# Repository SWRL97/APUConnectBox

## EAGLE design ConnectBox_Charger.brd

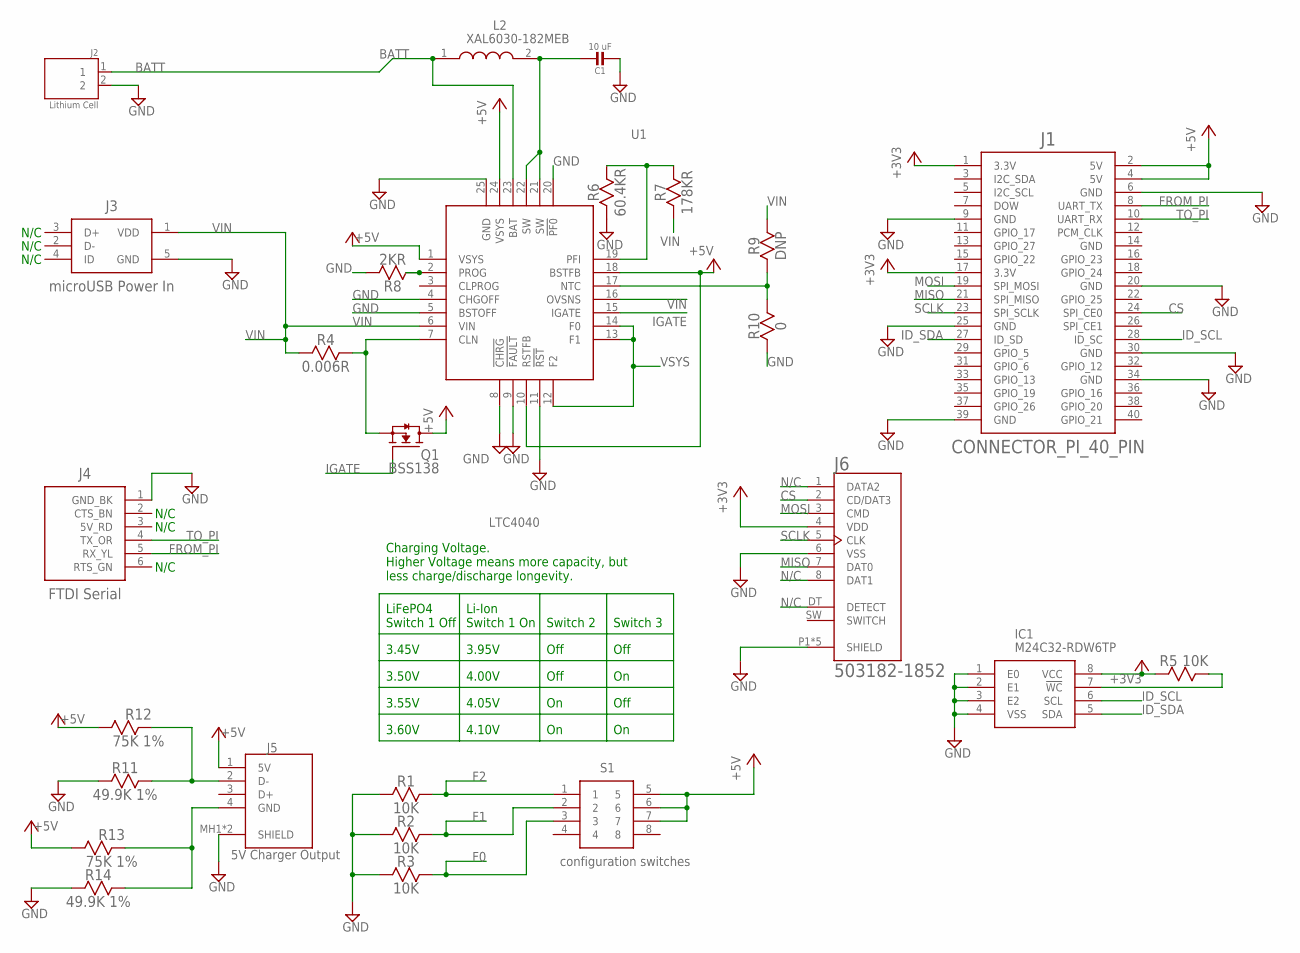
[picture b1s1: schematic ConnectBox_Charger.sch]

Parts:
C1: 10 uF; MICROBUILDER_0805_10MGAP
IC1: M24C32-RDW6TP; SOP65P640X120-8N
J1: CONNECTOR_PI_40_PIN; 2X20
J2: Lithium Cell; JST_S2B-PH-SM4-TB(LF)(SN)
J3: microUSB Power In; FRAMATOME_10118194-0001LF
J4: FTDI Serial; ESQ-106-XX-X-S
J5: 5V Charger Output; SS52100001
J6: 503182-1852; MOLEX_503182-1852
L2: XAL6030-182MEB; XAL6030182MEB
Q1: BSS138
R1, R2, R3, R5: 10K; RESC1608X55L25N
R4: 0.006R; RESC1608X55L25N
R6: 60.4KR; RESC1608X55L25N
R7: 178KR; RESC1608X55L25N
R8: 2KR; RESC1608X55L25N
R9: DNP; RESC1608X55L25N
R10: 0; RESC1608X55L25N
R11, R14: 49.9K 1%; RESC1608X55L25N
R12, R13: 75K 1%; RESC1608X55L25N
S1: configuration switches; 219-4LPST
U1: LTC4040; QFN50P500X400X80-25N

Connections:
+3V3: IC1.8 (VCC), J1.1 (3.3V), J1.17 (3.3V), J6.4 (VDD), R5.2
+5V: J1.2 (5V), J1.4 (5V), J5.1 (5V), Q1.D, R12.2, R13.2, S1.5, S1.6, S1.7, U1.1 (VSYS), U1.10 (RSTFB), U1.18 (BSTFB), U1.24 (VSYS)
BATT: J2.1, L2.1, U1.23 (BAT)
CS: J1.24 (SPI_CE0), J6.2 (CD/DAT3)
F0: R3.2, S1.3
F1: R2.2, S1.2
F2: R1.2, S1.1
FROM_PI: J1.8 (UART_TX), J4.5 (RX_YL)
GND: C1.2, IC1.1 (E0), IC1.2 (E1), IC1.3 (E2), IC1.4 (VSS), J1.6 (GND), J1.9 (GND), J1.20 (GND), J1.25 (GND), J1.30 (GND), J1.34 (GND), J1.39 (GND), J2.2, J3.5 (GND), J4.1 (GND_BK), J5.MH1 (SHIELD), J5.MH2 (SHIELD), J6.6 (VSS), J6.P1 (SHIELD), J6.P2 (SHIELD), J6.P3 (SHIELD), J6.P4 (SHIELD), J6.P5 (SHIELD), R1.1, R2.1, R3.1, R6.1, R8.2, R10.1, R11.2, R14.2, U1.4 (CHGOFF), U1.5 (BSTOFF), U1.8 (!CHRG), U1.9 (!FAULT), U1.11 (!RST), U1.20 (!PF0), U1.25 (GND)
ID_SCL: IC1.6 (SCL), J1.28 (ID_SC)
ID_SDA: IC1.5 (SDA), J1.27 (ID_SD)
IGATE: Q1.G, U1.15 (IGATE)
MISO: J1.21 (SPI_MISO), J6.7 (DAT0)
MOSI: J1.19 (SPI_MOSI), J6.3 (CMD)
unnamed: Q1.S, R4.2, U1.7 (CLN)
unnamed: IC1.7 (!WC), R5.1
unnamed: R6.2, R7.2, U1.19 (PFI)
unnamed: C1.1, L2.2, U1.21 (SW), U1.22 (SW)
unnamed: R8.1, U1.2 (PROG)
unnamed: J5.4 (GND), R13.1, R14.1
unnamed: R9.1, R10.2, U1.17 (NTC)
unnamed: J5.2 (D-), R11.1, R12.1
N/C: J6.1 (DATA2), J6.8 (DAT1), J6.DT (DETECT)
SCLK: J1.23 (SPI_SCLK), J6.5 (CLK)
TO_PI: J1.10 (UART_RX), J4.4 (TX_OR)
VIN: J3.1 (VDD), R4.1, R7.1, R9.2, U1.6 (VIN), U1.16 (OVSNS)
VSYS: U1.12 (F2), U1.13 (F1), U1.14 (F0)

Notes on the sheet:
N/C
Li-Ion Switch 1 On
Switch 3
LiFePO4 Switch 1 Off
Off
Switch 2
3.45V
3.95V
3.50V
4.00V
3.55V
4.05V
3.60V
4.10V
Charging Voltage. Higher Voltage means more capacity, but less charge/discharge longevity.

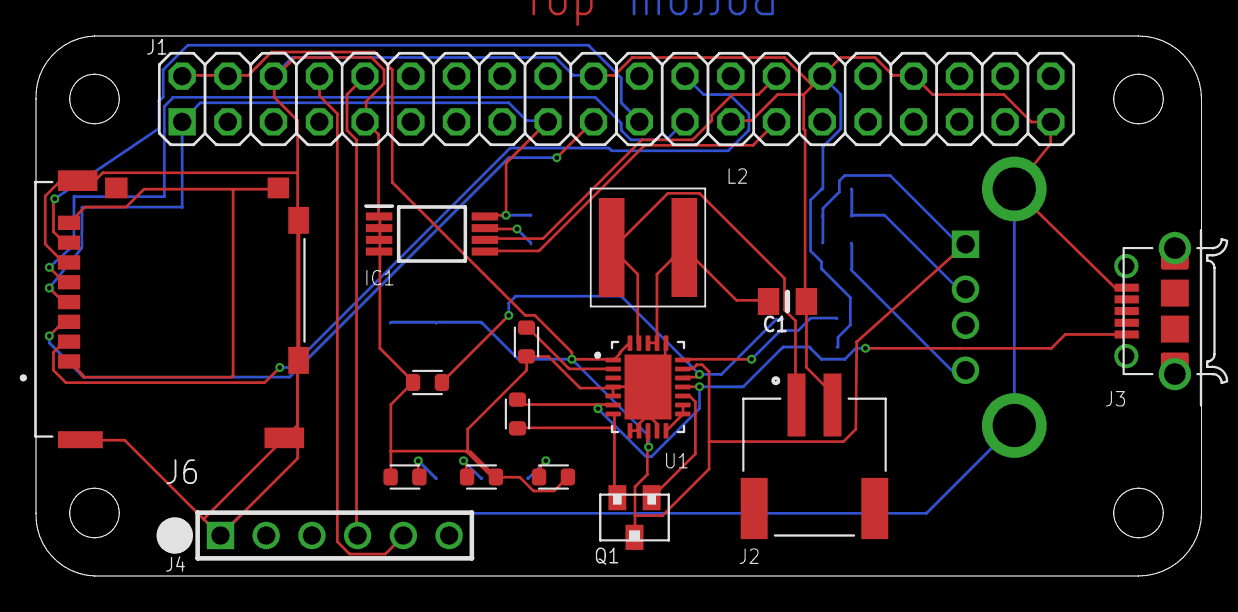
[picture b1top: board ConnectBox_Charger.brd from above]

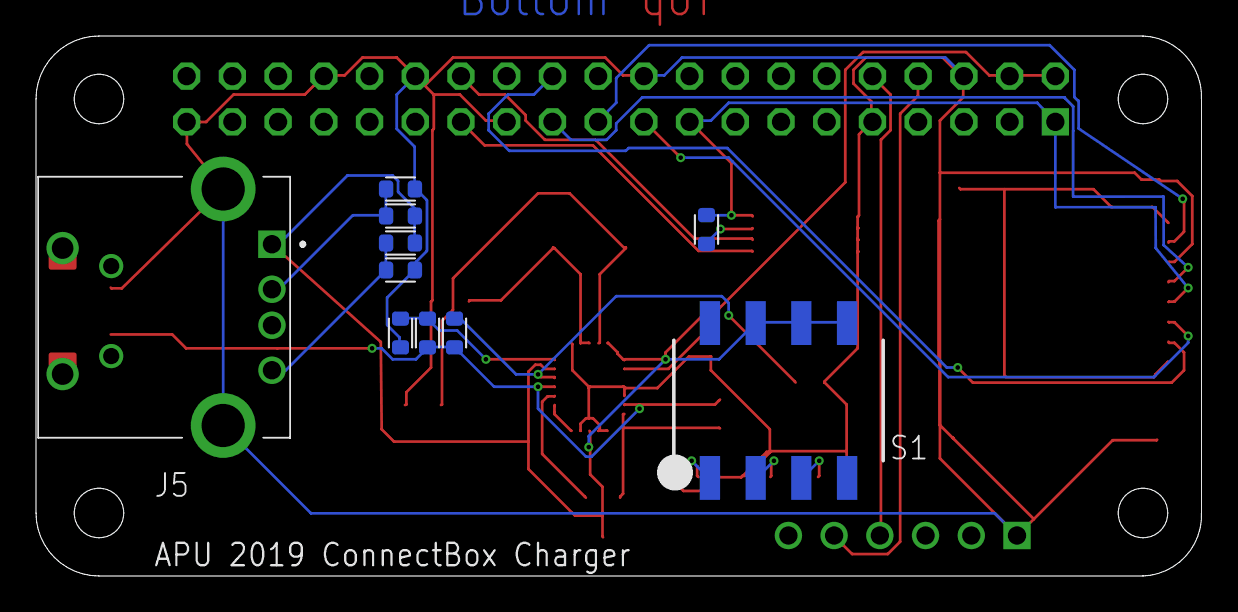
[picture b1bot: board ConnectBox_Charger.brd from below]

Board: 2 copper layers, 64.8 x 30.0 mm, 26 parts (10 on the bottom side), 27 nets.

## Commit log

2019-04-02 Create Steps for Raspberry Pi
2019-04-02 Update Steps for Raspberry Pi
2019-04-08 almost done just need to connect the SD holder to pins
2019-04-11 hopefully the last version with the charger
2019-04-16 Final push ready for ordering as the complete charging accessory for the MAF wifi box project.PCB will connect to RaspPI0W which will distribute wifi and hold essential software. The PCB will hold co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
2019-04-18 hope fully final push, did not change t/b restrict or t/b keepout can change tonight if need be
